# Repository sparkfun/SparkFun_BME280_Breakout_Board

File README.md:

SparkFun BME280
===============

[*SparkFun BME280 (SEN-13676)*](https://www.sparkfun.com/products/13676)

The Bosch BME280 sensor measures atmospheric pressure from 30kPa to 110kPa as well as relative humidity and temperature.  The SparkFun breakout provides a 3.3v SPI interface and a 5v tolerant I2C interface (has pull-up resistors to 3.3v).

Repository Contents
-------------------

* **/Documentation** - Data sheets, additional product information
* **/Hardware** - Eagle design files (.brd, .sch)
* **/Production** - Production panel files (.brd)

Documentation
--------------
* **[Library](https://github.com/sparkfun/SparkFun_BME280_Arduino_Library)** - Arduino library for the BME280.
* **[Hookup Guide](https://learn.sparkfun.com/tutorials/bme280-breakout-hookup-guide)** - Basic hookup guide for the SparkFun BME280.
* **[SparkFun Fritzing repo](https://github.com/sparkfun/Fritzing_Parts)** - Fritzing diagrams for SparkFun products.
* **[SparkFun 3D Model repo](https://github.com/sparkfun/3D_Models)** - 3D models of SparkFun products. 

Product Versions
----------------
* [*SEN-13676*](https://www.sparkfun.com/products/13676)

Version History
---------------

* [V_1.0.0](https://github.com/sparkfun/SparkFun_BME280_Breakout_Board/tree/V_1.0.0) - Public release.
* [V_1.1.0](https://github.com/sparkfun/SparkFun_BME280_Breakout_Board/tree/V_1.1.0) - Squashed arduino library changes.

License Information
-------------------

This product is _**open source**_! 

Please review the LICENSE.md file for license information. 

If you have any questions or concerns on licensing, please contact techsupport@sparkfun.com.

Distributed as-is; no warranty is given.

- Your friends at SparkFun.

_<COLLABORATION CREDIT>_

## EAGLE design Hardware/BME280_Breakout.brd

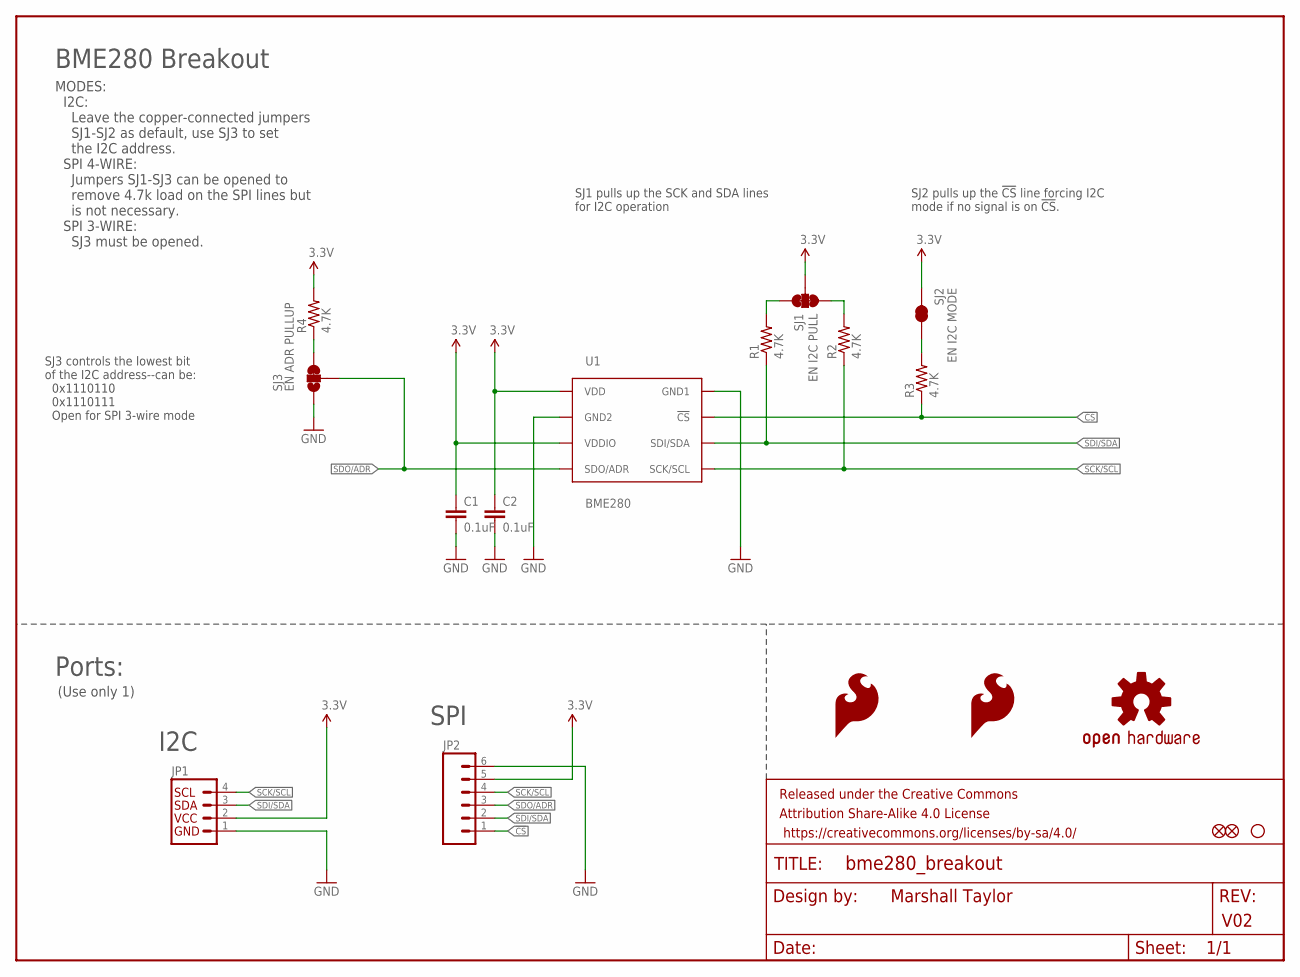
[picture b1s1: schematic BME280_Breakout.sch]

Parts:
C1, C2: 0.1uF; 0603-CAP
FID1, FID2: FIDUCIAL1X2; FIDUCIAL-1X2
FRAME1: FRAME-LETTER; CREATIVE_COMMONS
JP1: I2C_STANDARD_NO_SILK; 1X04_NO_SILK
JP2: M06NO_SILK_FEMALE_PTH; 1X06_NO_SILK
LOGO1, LOGO2: SFE_LOGO_FLAME.1_INCH; SFE_LOGO_FLAME_.1
LOGO3: OSHW-LOGOS; OSHW-LOGO-S
R1, R2, R3, R4: 4.7K; 0603-RES
SJ1: EN I2C PULL; PAD-JUMPER-3-3OF3_NC_BY_TRACE_YES_SILK_FULL_BOX
SJ2: EN I2C MODE; PAD-JUMPER-2-NC_BY_TRACE_YES_SILK
SJ3: EN ADR PULLUP; PAD-JUMPER-3-2OF3_NC_BY_TRACE_YES_SILK_FULL_BOX
STANDOFF4: STAND-OFF
U1: BME280; BME280_LGA

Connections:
3.3V: C1.1, C2.1, JP1.2, JP2.5, R4.2, SJ1.2, SJ2.2, U1.P$6 (VDDIO), U1.P$8 (VDD)
!CS: JP2.1, R3.1, U1.P$2 (!CS)
GND: C1.2, C2.2, JP1.1, JP2.6, SJ3.1, U1.P$1 (GND1), U1.P$7 (GND2)
unnamed: R1.2, SJ1.3
unnamed: R2.2, SJ1.1
unnamed: R3.2, SJ2.1
unnamed: R4.1, SJ3.3
SCK/SCL: JP1.4, JP2.4, R2.1, U1.P$4 (SCK/SCL)
SDI/SDA: JP1.3, JP2.2, R1.1, U1.P$3 (SDI/SDA)
SDO/ADR: JP2.3, SJ3.2, U1.P$5 (SDO/ADR)

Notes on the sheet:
Marshall Taylor
V02
BME280 Breakout
SJ3 controls the lowest bit of the I2C address--can be: 0x1110110 0x1110111 Open for SPI 3-wire mode
SJ1 pulls up the SCK and SDA lines for I2C operation
Ports:
(Use only 1)
I2C
SPI
MODES: I2C: Leave the copper-connected jumpers SJ1-SJ2 as default, use SJ3 to set the I2C address. SPI 4-WIRE: Jumpers SJ1-SJ3 can be opened to remove 4.7k load on the SPI lines but is not necessary. SPI 3-WIRE: SJ3 must be opened.
SJ2 pulls up the !CS! line forcing I2C mode if no signal is on !CS!.

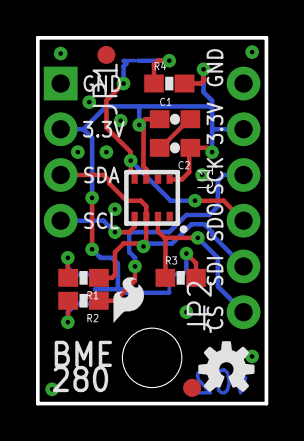
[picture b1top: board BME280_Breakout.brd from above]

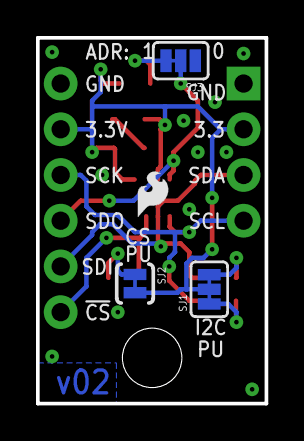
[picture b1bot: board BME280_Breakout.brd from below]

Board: 2 copper layers, 12.7 x 20.3 mm, 19 parts (4 on the bottom side), 10 nets.

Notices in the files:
parts and their libraries:
SparkFun-Capacitors: Licensing: Creative Commons ShareAlike 4.0 International - https://creativecommons.org/licenses/by-sa/4.0
SparkFun-Aesthetics: Released under the Creative Commons Attribution Share-Alike 4.0 License
SparkFun-Aesthetics: https://creativecommons.org/licenses/by-sa/4.0
